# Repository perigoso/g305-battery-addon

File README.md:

# g305-battery-addon

Add-On board for the G305, adds support for a lipo battery, chrger included, minimal modification to the shell required.

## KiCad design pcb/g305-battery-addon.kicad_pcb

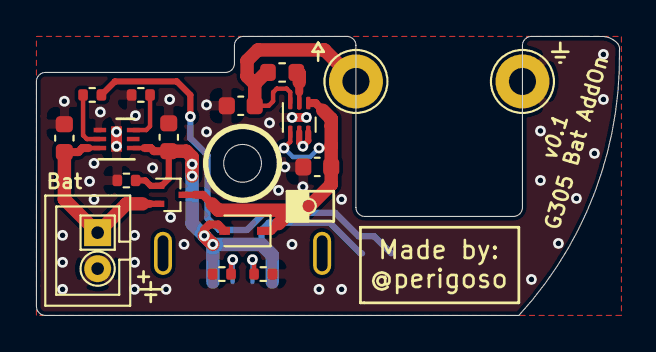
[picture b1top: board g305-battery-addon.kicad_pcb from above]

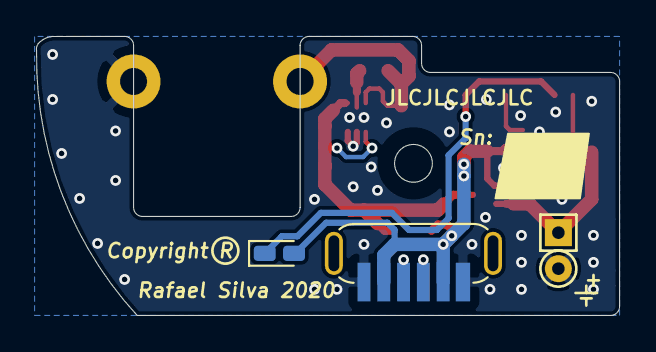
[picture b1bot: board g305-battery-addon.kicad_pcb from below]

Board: 2 copper layers, 32.4 x 15.5 mm, 20 parts (2 on the bottom side), 11 nets.

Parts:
C101, C102, C103, C104: 4.7uF; C_0603_1608Metric
D101: YLW; LED_0603_1608Metric_Castellated
D102: D_Small; D_SOD-323
J101: USB_C_Receptacle_USB2.0; USB_C_Receptacle_6P_Vertical
L101: 0.47uH; L_0603_1608Metric
Q101: NTA4151PT1G; SOT-323_SC-70
R101, R102: 5.11k; R_0402_1005Metric
R103, R104: 2k; R_0402_1005Metric
R105: 10k; R_0402_1005Metric
TP101: GND; TestPoint_THTPad_D1.5mm_Drill0.7mm
TP102: VBAT; TestPoint_THTPad_1.5x1.5mm_Drill0.7mm
TP103: GND; TestPoint_THTPad_D3.0mm_Drill1.5mm
TP104: VOUT; TestPoint_THTPad_D3.0mm_Drill1.5mm
U101: MCP73830; DFN-6-1EP_2x2mm_P0.5mm_EP0.61x1.42mm
U102: MCP23030-GY; MLF-6-1EP_1.6x1.6mm_P0.5mm_EP0.5x1.26mm

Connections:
GND: C101.2, C102.2, C103.1, C104.1, J101.A12, J101.B12, R101.1, R102.2, R104.2, R105.1, TP101.1, TP103.1, U101.1, U101.7, U102.5, U102.6, U102.7
unnamed: C101.1, D101.2, D102.2, J101.A9, J101.B9, Q101.1, R105.2, U101.4
unnamed: C102.1, Q101.2, TP102.1, U101.3
unnamed: C103.2, D102.1, Q101.3, U102.1, U102.4
unnamed: C104.2, L101.2, TP104.1, U102.3
unnamed: D101.1, R103.2
unnamed: J101.A5, R102.1
unnamed: J101.B5, R101.2
unnamed: L101.1, U102.2
unnamed: R103.1, U101.2
unnamed: R104.1, U101.6

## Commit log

2020-12-24 Add Rev0.1

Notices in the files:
pcb/g305-battery-addon.kicad_pcb:
This work is licensed under
Copyright R
